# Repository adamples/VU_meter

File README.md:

# OLED display VU meter — AVR/Arduino project

This project is to create digital version of a nice gadget that adds a little magic 
to any audio equipment: a [VU meter](https://en.wikipedia.org/wiki/VU_meter). Main design
goals are:
  - 2-channel operation,
  - as close to real VU-meter specification as possible,
  - high FPS, 60+ — no visible jumping of needle, as is common in other designs.

Project uses AVR ATMega88/168/328 (and ATMega48 if possible), so should be compatibile with
Arduino Uno boards. Small (and cheap) monochrome OLED modules with SSD1306 or SH1106 driver are 
employed as displays. Unlike other AVR VU meters that you can find on the web this one uses
quite complex analog circuitry (it can be much simpler if you are not as interested as me in
up-to-specs VU meter emulation).

Here's a video showing test of VU meter prototype:

## Building The Project

To build hex file you'll need:
  - avr-gcc,
  - GNU make,
  - Python 2.7 or 3.
For windows you can use this distribution of gcc and make: http://blog.zakkemble.co.uk/avr-gcc-builds/

Before compilation please modify [src/config.h](src/config.h) file to set proper OLED controller type and [Makefile](Makefile) to set uC type and oscillator frequency (F_CPU).

To create hex file type:
```
$ make all
```
This will create `build/main.hex` that you can use to flash your device.

__Note: This is Work In Progress design. To make it work for you you'll most probably need to modify it in one way or another.__

## Hardware Design

If you would like to make VU meter yourself here are some useful files for you:
  - [hardware/vu_meter.sch](hardware/vu_meter.sch) — schematic (in Eagle 8 format)
  - [hardware/vu_meter.brd](hardware/vu_meter.brd) — PCB design (in Eagle 8 format)
  - [hardware/vu_meter_sch.pdf](hardware/vu_meter_sch.pdf) — schematic as PDF
  - [hardware/bom.ods](hardware/bom.ods) — bill of materials (open document)
  - [hardware/vu_meter.zip](hardware/vu_meter.zip) — gerber files ready for production

PCB is designed as a module to be included in other devices so all signals are connected using goldpin headers:

There is also Arduino UNO shield (rev.3) design, altough it's not very polished version:
  - [hardware/arduino_shield.sch](hardware/arduino_shield.sch) — schematic (in Eagle 8 format)
  - [hardware/arduino_shield.brd](hardware/arduino_shield.brd) — PCB design (in Eagle 8 format)

Full documentation will be included in the future, as the project progresses.

For now here's very high-level block diagram of the device:

Second analog channel and OLED display were omitted for the sake of brevity.

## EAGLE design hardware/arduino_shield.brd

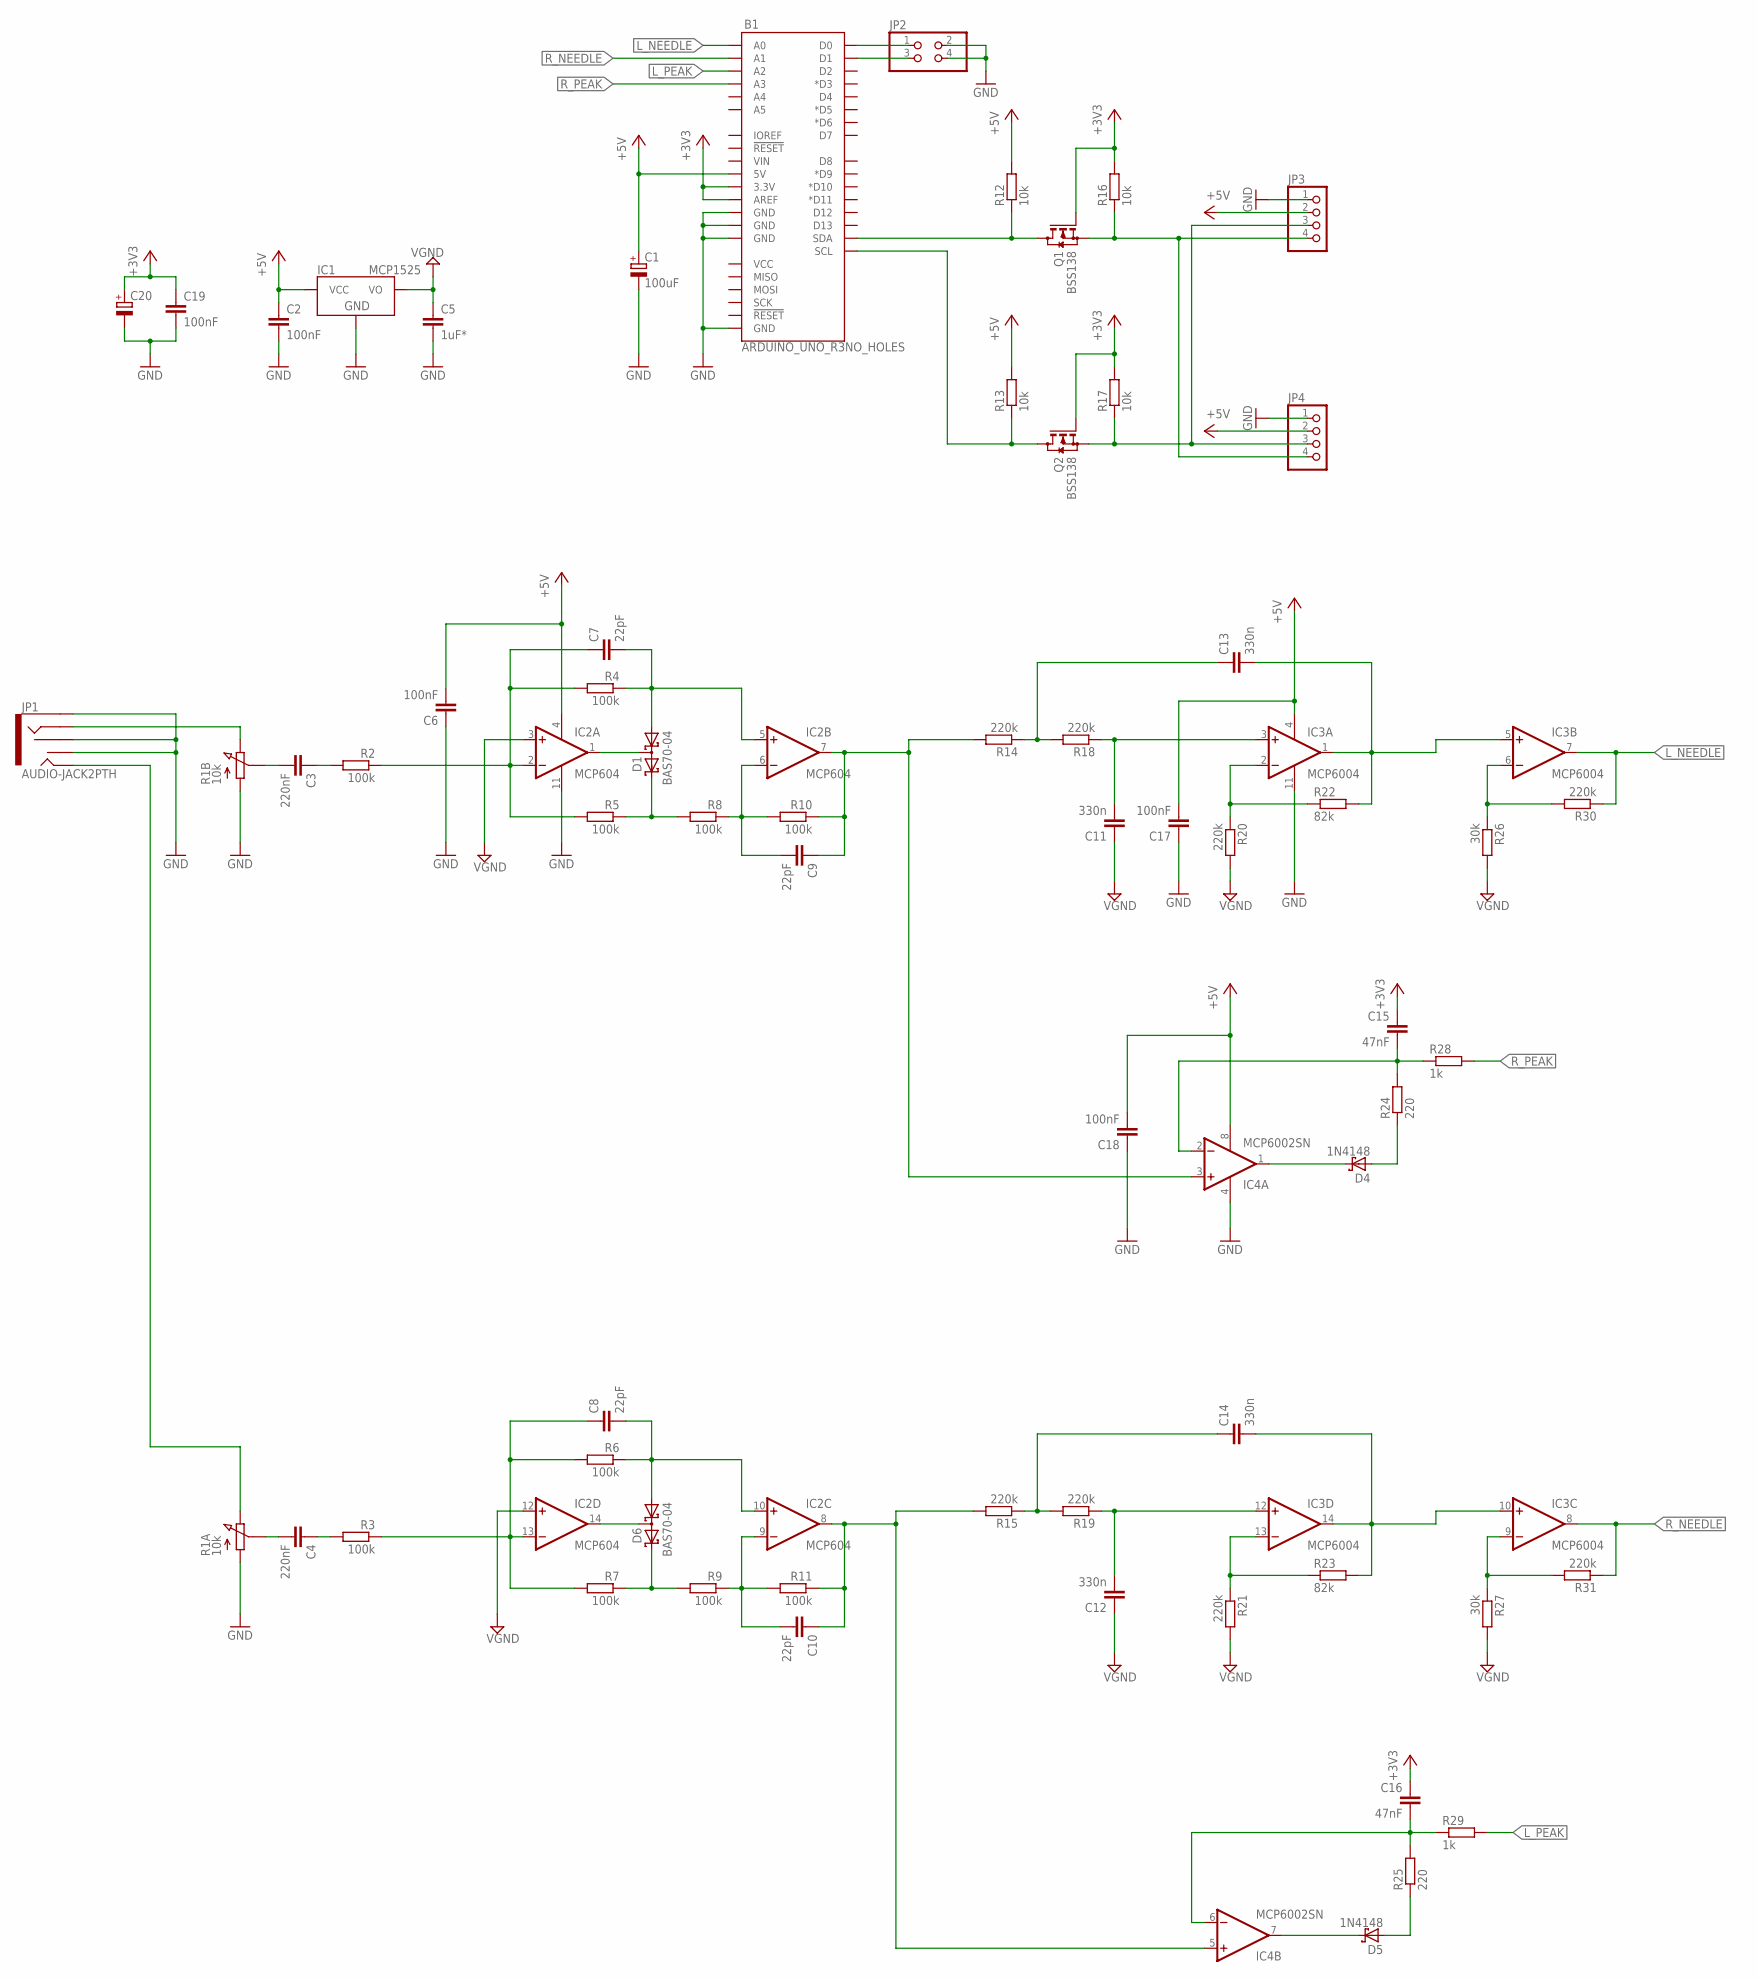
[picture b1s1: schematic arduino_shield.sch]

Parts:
B1: ARDUINO_UNO_R3NO_HOLES; ARDUINO_R3_NO_HOLES
C1: 100uF; B/3528-21R
C2, C6, C17, C18, C19: 100nF; C0805
C3, C4: 220nF; C0805
C5: 1uF*; C0805
C7, C8, C9, C10: 22pF; C0805
C11, C12, C13, C14: 330n; C0805
C15, C16: 47nF; C0805
C20: CPOL-EUA/3216-18R; A/3216-18R
D1, D6: BAS70-04; SOT23
D4, D5: 1N4148; SOD323_ST
IC1: MCP1525; SOT23-3
IC2: MCP604; SO14
IC3: MCP6004; SO14
IC4: MCP6002SN; SO08
JP1: AUDIO-JACK2PTH; AUDIO-JACK
JP2: PINHD-2X2; 2X02
JP3, JP4: PINHD-1X4; 1X04
Q1, Q2: BSS138; SOT23
R1: 10k; POT1
R2, R3, R4, R5, R6, R7, R8, R9, R10, R11: 100k; R0805
R12, R13, R16, R17: 10k; R0805
R14, R15, R30, R31: 220k; M0805
R18, R19, R20, R21: 220k; R0805
R22, R23: 82k; R0805
R24, R25: 220; R0805
R26, R27: 30k; M0805
R28, R29: 1k; R0805

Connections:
+3V3: B1.3.3V, B1.AREF, C15.1, C16.1, C19.1, C20.+, Q1.1 (G), Q2.1 (G), R16.2, R17.2
+5V: B1.5V, C1.+, C2.1, C6.2, C17.2, C18.2, IC1.1 (VCC), IC2.4 (V+), IC3.4 (V+), IC4.8 (V+), JP3.2, JP4.2, R12.2, R13.2
GND: B1.GND@1 (GND), B1.GND@2 (GND), B1.GND@3 (GND), B1.GND@4 (GND), C1.-, C2.2, C5.2, C6.1, C17.1, C18.1, C19.2, C20.-, IC1.3 (GND), IC2.11 (V-), IC3.11 (V-), IC4.4 (V-), JP1.RSH, JP1.SLEEVE, JP1.TSH, JP2.2, JP2.4, JP3.1, JP4.1, R1.1-1 (A-1), R1.2-1 (A-1)
GND1: C5.1, C11.1, C12.1, IC1.2 (VO), IC2.3 (+IN), IC2.12 (+IN), R20.2, R21.2, R26.2, R27.2
L_NEEDLE: B1.A0, IC3.7 (OUT), R30.1
L_PEAK: B1.A2, R29.2
unnamed: IC3.6 (-IN), R26.1, R30.2
unnamed: B1.D0, JP2.1
unnamed: B1.SDA, Q1.3 (D), R12.1
unnamed: D5.A, R25.1
unnamed: B1.SCL, Q2.3 (D), R13.1
unnamed: B1.D1, JP2.3
unnamed: D5.C, IC4.7 (OUT)
unnamed: C13.1, R14.1, R18.2
unnamed: C13.2, IC3.1 (OUT), IC3.5 (+IN), R22.2
unnamed: C16.2, IC4.6 (-IN), R25.2, R29.1
unnamed: IC3.9 (-IN), R27.1, R31.2
unnamed: C11.2, IC3.3 (+IN), R18.1
unnamed: IC3.2 (-IN), R20.1, R22.1
unnamed: D1.2 (C2), R5.1, R8.2
unnamed: C12.2, IC3.12 (+IN), R19.1
unnamed: C3.2, R1.2-2 (S-2)
unnamed: C7.1, IC2.2 (-IN), R2.1, R4.2, R5.2
unnamed: D4.C, IC4.1 (OUT)
unnamed: IC3.13 (-IN), R21.1, R23.1
unnamed: C14.1, R15.1, R19.2
unnamed: C7.2, D1.1 (A1), IC2.5 (+IN), R4.1
unnamed: D1.3 (C1A2), IC2.1 (OUT)
unnamed: C9.2, IC2.6 (-IN), R8.1, R10.2
unnamed: C14.2, IC3.10 (+IN), IC3.14 (OUT), R23.2
unnamed: D6.2 (C2), R7.1, R9.2
unnamed: C8.1, IC2.13 (-IN), R3.1, R6.2, R7.2
unnamed: C8.2, D6.1 (A1), IC2.10 (+IN), R6.1
unnamed: D6.3 (C1A2), IC2.14 (OUT)
unnamed: C10.2, IC2.9 (-IN), R9.1, R11.2
unnamed: C10.1, IC2.8 (OUT), IC4.5 (+IN), R11.1, R15.2
unnamed: C4.2, R1.1-2 (S-2)
unnamed: C4.1, R3.2
unnamed: C3.1, R2.2
unnamed: JP1.RING, R1.2-3 (E-3)
unnamed: JP1.TIP, R1.1-3 (E-3)
unnamed: C15.2, IC4.2 (-IN), R24.2, R28.1
unnamed: D4.A, R24.1
unnamed: C9.1, IC2.7 (OUT), IC4.3 (+IN), R10.1, R14.2
R_NEEDLE: B1.A1, IC3.8 (OUT), R31.1
R_PEAK: B1.A3, R28.2
SCL: JP3.3, JP4.3, Q2.2 (S), R17.1
SDA: JP3.4, JP4.4, Q1.2 (S), R16.1

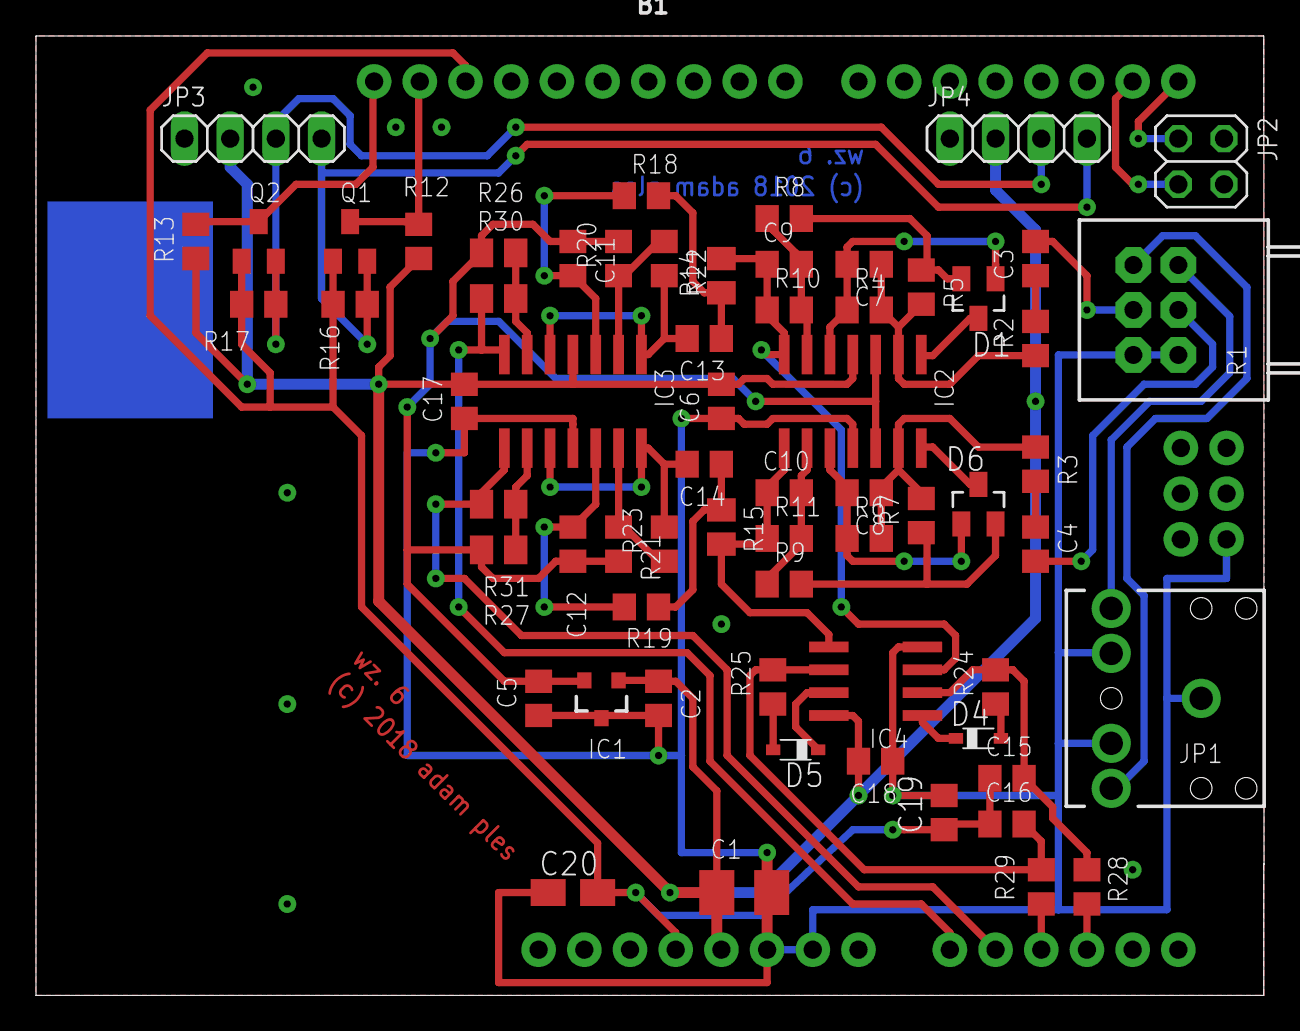
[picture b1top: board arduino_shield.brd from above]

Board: 2 copper layers, 68.3 x 53.3 mm, 66 parts (0 on the bottom side), 48 nets.

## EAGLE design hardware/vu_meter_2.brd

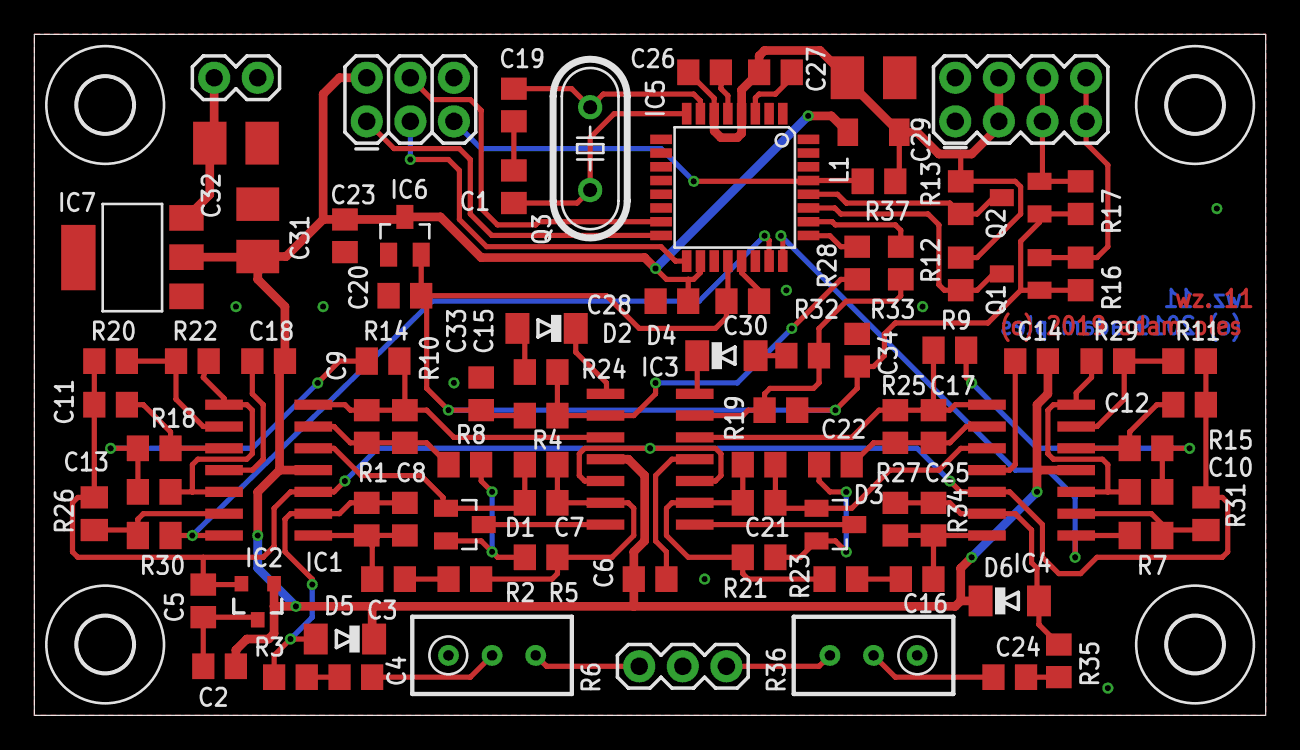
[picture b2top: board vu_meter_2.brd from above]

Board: 2 copper layers, 71.7 x 39.7 mm, 96 parts (0 on the bottom side), 60 nets.

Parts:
C1, C19: 22pF; C0805
C2, C6, C14, C18, C26, C27, C28, C30, C33, C34: 100nF; C0805
C3, C16: 470nF; C0805
C4, C24: 220nF; C0805
C5, C23: 1uF; C0805
C7, C9, C17, C21: 220pF; C0805
C8, C25: 33pF; C0805
C10, C13: 330n; C0805
C11, C12: 330nF; C0805
C15, C22: 47nF; C0805
C20: 10uF; C0805
C29, C31: 100uF; B/3528-21R
C32: 10uF; B/3528-21R
D1, D3: BAS70-04; SOT23
D2, D4: 1N4148; MINIMELF
D5, D6: BAT85; MINIMELF
H1, H2, H3, H4: MOUNT-HOLE3.2; 3,2
IC1: MCP1525; SOT23-3
IC2, IC4: MCP6004; SO14
IC3: MCP604SL; SO14
IC5: MEGA88; TQFP32-08
IC6: MCP1700 3V3; SOT23
IC7: REG1117; SOT223
J1: 455-1750-1-ND; 1X03
J2: 1X02
J3: 2X3
J4: 2X4
L1: 10uH; L3216C
Q1, Q2: BSS138; SOT23
Q3: HC49/S
R1, R11, R15, R18, R20, R34: 220k; R0805
R2, R4, R5, R8, R10, R12, R13, R16, R17, R19, R21, R23, R25, R27, R37: 10k; R0805
R3, R35: 22k; R0805
R6, R36: 10k; RTRIM3296W
R7, R9, R14, R30: 220k; M0805
R22, R29: 82k; R0805
R24, R32: 220; R0805
R26, R31: 47k; M0805
R28, R33: 1k; R0805

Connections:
+3V3: C15.1, C20.1, C22.1, C30.1, C33.2, C34.2, IC5.20, IC6.2, Q1.1, Q2.1, R16.2, R17.2
+5V: C2.1, C6.2, C14.2, C18.2, C23.1, C28.1, C31.+, D5.C, D6.C, IC1.1, IC2.4, IC3.4, IC4.4, IC5.18, IC6.3, IC7.2, J3.2, L1.2
GND: C1.1, C2.2, C5.2, C6.1, C14.1, C18.1, C19.1, C20.2, C23.2, C26.2, C27.2, C28.2, C29.-, C30.2, C31.-, C32.-, C33.1, C34.1, IC1.3, IC2.11, IC3.11, IC4.11, IC5.3, IC5.5, IC5.21, IC6.1, IC7.1, J1.2, J2.1, J3.6, J4.1, J4.2, R6.1, R36.1
GND1: C5.1, C11.1, C12.1, IC1.2, IC2.3, IC3.5, IC3.10, IC4.12, R11.2, R20.2, R26.2, R31.2
IN: J1.3, R6.3
IN1: J1.1, R36.3
L_NEEDLE: IC2.14, IC5.23, R30.1
L_PEAK: IC5.25, R28.2
unnamed: IC2.13, R26.1, R30.2
unnamed: IC4.2, R7.2, R31.1
unnamed: C8.1, D5.A, IC2.2, R1.2, R3.1
unnamed: C4.1, R3.2
unnamed: C12.2, IC4.5, R15.1
unnamed: C4.2, R6.2
unnamed: C13.1, R14.1, R18.2
unnamed: C13.2, IC2.8, IC2.12, R22.2
unnamed: IC4.6, R11.1, R29.1
unnamed: D3.2, R21.1, R27.2
unnamed: C21.1, IC3.9, R19.2, R21.2, R23.1
unnamed: C11.2, IC2.10, R18.1
unnamed: IC2.9, R20.1, R22.1
unnamed: D1.2, R5.1, R8.2
unnamed: C21.2, D3.1, IC4.10, R19.1
unnamed: C3.2, C8.2, IC2.1, R1.1
unnamed: C7.1, IC3.6, R2.1, R4.2, R5.2
unnamed: D2.C, IC3.1
unnamed: D3.3, IC3.8
unnamed: C17.2, IC4.9, R25.2, R27.1
unnamed: C16.2, C25.2, IC4.14, R34.1
unnamed: C16.1, R23.2
unnamed: C7.2, D1.1, IC2.5, R4.1
unnamed: D1.3, IC3.7
unnamed: C9.2, IC2.6, R8.1, R10.2
unnamed: C10.1, R9.1, R15.2
unnamed: C10.2, IC4.3, IC4.7, R29.2
unnamed: C22.2, IC3.13, R32.2, R33.1
unnamed: D4.A, R32.1
unnamed: C17.1, IC3.12, IC4.8, R9.2, R25.1
unnamed: D4.C, IC3.14
unnamed: C25.1, D6.A, IC4.13, R34.2, R35.1
unnamed: C24.1, R35.2
unnamed: C24.2, R36.2
unnamed: C19.2, IC5.7, Q3.2
unnamed: C1.2, IC5.8, Q3.1
unnamed: IC5.15, J3.4
unnamed: C3.1, R2.2
unnamed: IC5.17, J3.3
unnamed: IC5.16, J3.1
unnamed: IC5.29, J3.5, R37.1
unnamed: C15.2, IC3.2, R24.2, R28.1
unnamed: D2.A, R24.1
unnamed: C32.+, IC7.3, J2.2
unnamed: C9.1, IC2.7, IC3.3, R10.1, R14.2
R_NEEDLE: IC4.1, IC5.24, R7.1
R_PEAK: IC5.26, R33.2
SCL: J4.5, J4.6, Q2.2, R17.1
SCL1: IC5.28, Q2.3, R13.1
SDA: J4.7, J4.8, Q1.2, R16.1
SDA1: IC5.27, Q1.3, R12.1
VCC: C26.1, C27.1, C29.+, IC5.4, IC5.6, J4.3, J4.4, L1.1, R12.2, R13.2, R37.2

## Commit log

2017-11-05 Added scale design documentation
2017-11-13 Simple application with VU meter background and flashing peak indicator.
    - asynchronous I2C library with buffering and client queue,
    - initial SSD1306 routines with support for 2 displays connected via I2C,
    - converting images from PNG to C code,
    - drawing images on displays,
    - ~3KB of FLASH used (including images).
2017-11-13 Added Geany project files to gitignore
2017-11-13 I2C queue changed from single-linked list to ring buffer.
    Added debug LCD display, only for development.
2017-11-23 Introduced composite rendering (very slow)
    benchmark.c: added to profile rendering code
    display.c: composite rendering implementation
    drawing.c: needle sprite rendering
    i2c.c: removed debug LED indicator, added more assertions
    lcd.c: resetting pins after transmission
    ring_buffer.c: refactored assertions for external use, added function
2017-11-23 Added photo from 2017-11-23 for journal
2017-11-23 Added lst files and main to gitignore
2017-11-23 Created journal file to track progress and ideas
    ... including entry for today.
2017-11-26 Double buffering implemented in I2C driver
2017-11-26 Added generated C files to gitignore
2017-11-26 Added entry to journal
2017-11-30 I2C rewrite work in progress
2017-11-30 I2C driver rewritten and operational
2017-11-30 Removed unneccessary volatile qualifiers
2017-11-30 Added caching of next command to I2C driver
2017-11-30 Drawing renamed to needle_sprite (reflecting the content)
2017-11-30 Code cleanup
    - I2C hw functions moved to it's own header
    - image sprite moved to separate object file
    - removed accidentaly added lst file
    - min/max functions moved to header
2017-11-30 Better resolution benchmark + minor bug fixes
2017-11-30 Added README
    Including short description of the project and link to youtube video.
2017-12-01 Rework and cleanup of display and SSD1306 driver
2017-12-07 Added precomputed needle coordinates
    ... in order to remove floating point math dependency.
2017-12-07 Added fixed point math library
2017-12-09 Benchmark implemented in main
2017-12-14 OLED display initialization moved to driver
2017-12-14 Needles are now controlled by separate ADC channels
2017-12-15 Partial rendering implemented
2017-12-18 Started implementation of diff-based rendering
2017-12-19 Partial rendering optimalization
    Implemented pruning overlapping update regions which results in
    FPS gain of up to 100% (~200FPS max).
2017-12-19 Added synchronous I2C driver
    Slower, but much smaller in terms of code size and memory usage.
2017-12-20 .c.inc files renamed to just .c
2017-12-28 Link to youtube video updated in README
2017-12-29 Block diagram added to images
2017-12-30 Updated block diagram & electrical connection diagram for displays
2017-12-30 Initial design documentation added to README
2017-12-30 Fixed typo in README
2017-12-30 Updated link to youtube video in README
2017-12-31 Minor fixes to OLED connection diagram
2018-01-10 Fixed swapped MOSFET pins on OLED connection diagram
2018-01-19 Added analog simulation (rectifier + ballistics) schematic
2018-01-19 Short description of analog circuitry added to README.md
2018-02-07 Reduced interrupt overhead for sending data over I2C
2018-03-18 Makefile updated for separate src and build directories
2018-03-18 Cleaned up main & adapted second screen to show FPS
2018-03-18 Fixed configuration changed by mistake
2018-03-18 Additional fixes for issues in Makefile
2018-03-20 Image conversion script is now standalone
    ... and supports both Python 2 and 3, but only 24-bit bitmaps. Also
    does dithering.
2018-05-03 Added generated files to source control
2018-05-05 Disabled second display
2018-05-14 Fixed update of peak indicator
2018-05-21 Added preliminary Eagle files (schematic + PCB)
2018-05-21 Revert "Added preliminary Eagle files (schematic + PCB)"
    This reverts commit eb782ed89749604550bede436b3c459ceac1df2c.
2018-06-04 Preparation to add different OLED driver
2018-06-04 Fixed removing hex and eep files in Makefile (clean)
2018-06-04 Added missing generated files to gitignore
2018-06-04 Added preliminary support for SH1106 displays
2018-06-04 Updated README with information about SH1106 support
2018-08-04 Updated schematic and added bill of materials
2018-09-30 Updates to design & build process
2019-03-12 Changed I2C driver for lower flash footprint
2019-03-14 Several small improvements
2019-03-18 More flexible configuration
2019-03-19 Updated SSD1306 driver + additional artwork
2019-03-25 Changes to build system: introduced mods
2019-03-25 SSD1305 and SSD1309 drivers
2019-03-25 Added two new mods
2019-03-25 Fixed "reset to factory defaults" hw config
2019-03-25 Fixed display enabling delay
2019-04-01 Added needle coordinates script back
2019-04-04 Additional configuration options
2019-04-07 Added hardware documentation
2019-04-07 Added PCB image
2019-04-07 Added gerber files and Arduino shield documentation
2019-04-07 Added information about hardware design to README
2019-04-08 Create LICENSE
2019-04-15 Fixed sch and brd names and added pdf schematic
2019-06-26 Added missing defines in config.h
2019-06-26 Fixed factory reset function
2019-06-26 Automatic eeprom write on first use
    Manual writing of eeprom image is now not required
2019-06-26 Added script for making releases
2019-06-26 Fixed release script and watermark
2019-06-26 Additional files included in release
2020-12-01 Changed sprites order -- needle should be on top

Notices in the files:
hardware/arduino_shield.brd:
(c) 2018 adam ples
hardware/vu_meter_2.brd:
(c) 2019 adam ples
parts and their libraries:
SparkFun-Boards: Licensing: Creative Commons ShareAlike 4.0 International - https://creativecommons.org/licenses/by-sa/4.0
SparkFun: Licensing: CC v3.0 Share-Alike You are welcome to use this library for commercial purposes.
